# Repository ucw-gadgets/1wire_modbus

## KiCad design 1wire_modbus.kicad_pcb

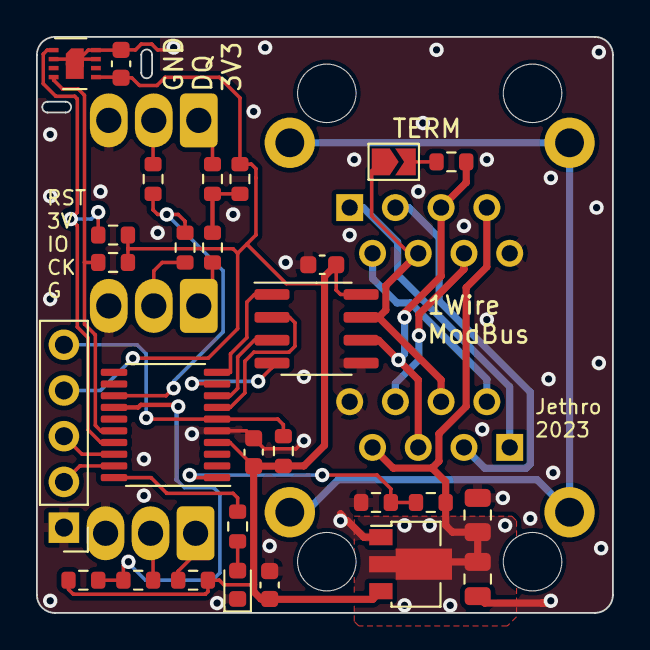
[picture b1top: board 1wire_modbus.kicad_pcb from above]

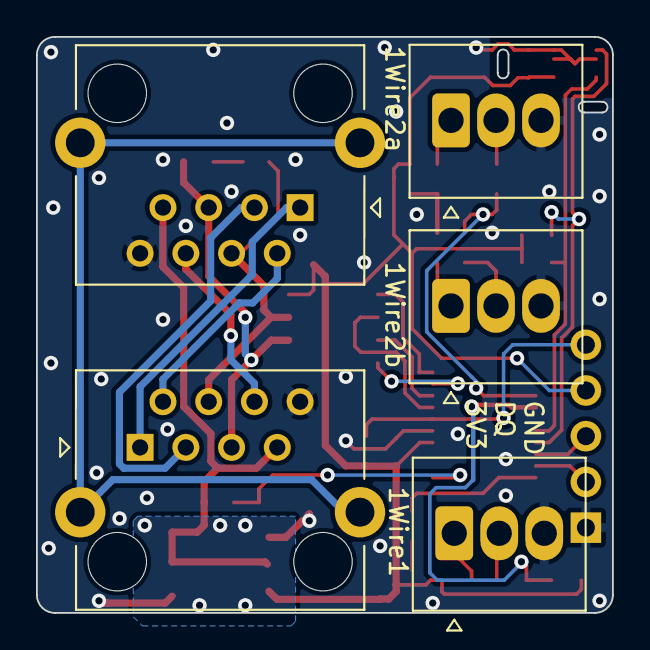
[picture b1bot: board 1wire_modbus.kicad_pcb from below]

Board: 2 copper layers, 32.0 x 32.0 mm, 33 parts (5 on the bottom side), 32 nets.

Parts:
C1, C6: 10u; C_0805_2012Metric
C2: 10u; C_0603_1608Metric
C3, C4, C5: 100n; C_0603_1608Metric
D1: LED; LED_0603_1608Metric
J1, J2: RJ45_Shielded; RJJS-88-A22-E1V
J3: 1WIRE1; 15EDGVC-2.5-03P-14
J4: PROG; PinHeader_1x05_P2.54mm_Vertical
J5: 1WIRE2; 15EDGVC-2.5-03P-14
J6: 1WIRE0; 15EDGVC-2.5-03P-14
JP1: TERM; SolderJumper-2_P1.3mm_Open_TrianglePad1.0x1.5mm
R1, R2, R4, R5: 120R; R_0603_1608Metric
R3, R13, R14: 2k7; R_0603_1608Metric
R6, R11, R15: 4k7; R_0603_1608Metric
R7, R8, R9: 330R; R_0603_1608Metric
R10, R12: 47k; R_0603_1608Metric
U1: HT75xx-1-SOT89; SOT-89-3
U2: SP3485EN; SOIC-8_3.9x4.9mm_P1.27mm
U3: STM32G030F6Px; TSSOP-20_4.4x6.5mm_P0.65mm
U4: SHT30-DIS; Sensirion_DFN-8-1EP_2.5x2.5mm_P0.5mm_EP1.1x1.7mm

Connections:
+3V3: C2.1, C3.1, C4.1, C5.1, J4.4, R2.1, R6.2, R12.1, R13.2, R14.2, R15.2, U1.3 (VOUT), U2.8 (VCC), U3.4 (VDD), U4.5 (VDD)
/1WIRE: R6.1, R7.1, U3.14 (PA7)
/1WIRE2: R8.1, R9.1, U3.13 (PA6)
/1WIREx: J1.6, J2.6
/A: J1.5, J2.5, R1.1, U2.6 (A)
/B: J1.4, J2.4, JP1.1 (A), U2.7 (B)
/DE: U2.3 (DE), U3.8 (PA1)
/LED: R3.2, U3.20 (PB3/PB4/PB5/PB6)
/RX: U2.1 (RO), U3.10 (PA3)
/SCL: R14.1, U3.16 (PA11/PA9), U4.4 (SCL)
/SDA: R13.1, U3.17 (PA12/PA10), U4.1 (SDA)
/SWCLK: J4.2, U3.19 (PA14/PA15)
/SWDIO: J4.3, U3.18 (PA13)
/TX: U2.4 (DI), U3.9 (PA2)
/V_SENSE: R10.1, R11.2, U3.1 (PB7/PB8)
/~RE: U2.2 (~RE), U3.7 (PA0)
/~RST: J4.5, R12.2, U3.6 (NRST)
GND: C1.2, C2.2, C3.2, C4.2, C5.2, C6.2, D1.1 (K), J1.8, J2.8, J3.3, J4.1, J5.3, J6.3, R11.1, U1.1 (GND), U2.5 (GND), U3.5 (VSS), U4.2 (ADDR), U4.7 (R), U4.8 (VSS), U4.9 (VSS)
unnamed: D1.2 (A), R3.1
unnamed: J1.1, J2.1
unnamed: J1.2, J2.2
unnamed: J1.3, J2.3
unnamed: J1.SH, J2.SH
unnamed: J3.1, R4.2
unnamed: J3.2, R8.2
unnamed: J5.1, R5.2
unnamed: J5.2, R9.2
unnamed: J6.1, R2.2
unnamed: J6.2, R7.2
unnamed: JP1.2 (B), R1.2
unnamed: R4.1, R5.1, R15.1
VCC: C1.1, C6.1, J1.7, J2.7, R10.2, U1.2 (VIN)

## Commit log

2024-01-17 First HW revision, libopencm3 finally working.
2024-01-17 Preparing for second thermometer.
2024-01-17 Working both channels.
2024-01-18 Added ADC, formatting.
